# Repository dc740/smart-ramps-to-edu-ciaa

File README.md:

# Smart-RAMPS to EDU-CIAA (Work in progress)
Adapter to be able to use a Smart RAMPS (3.3v) as an EDU-CIAA Poncho

It's not finished yet!

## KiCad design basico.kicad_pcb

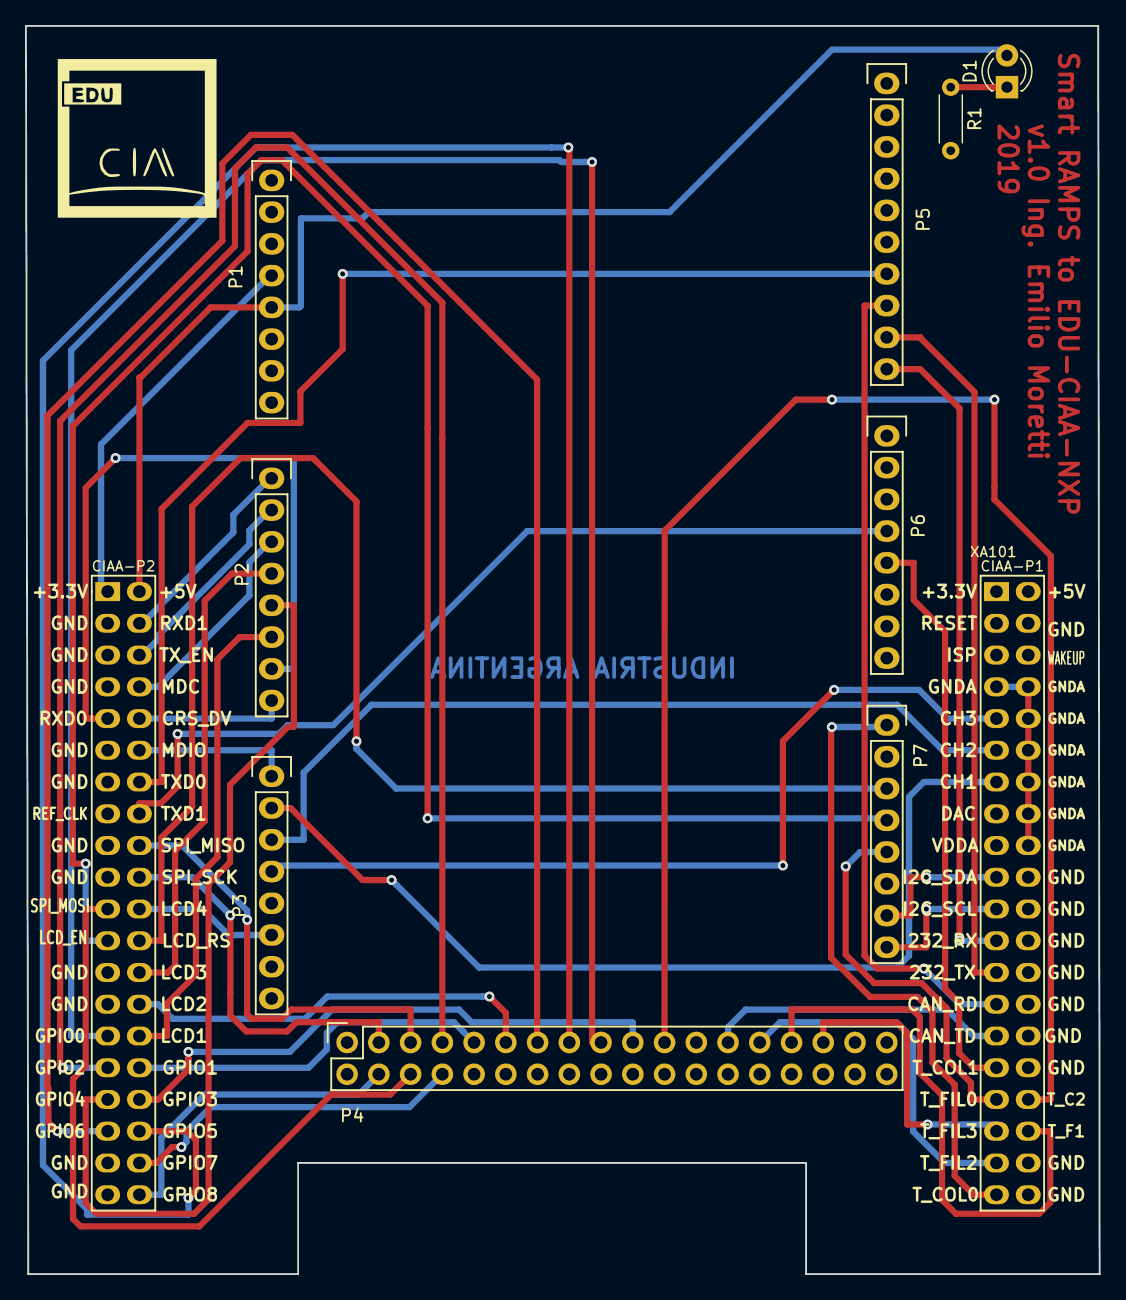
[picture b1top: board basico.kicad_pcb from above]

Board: 2 copper layers, 85.9 x 99.9 mm, 10 parts (0 on the bottom side), 46 nets.

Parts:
D1: LED; LED_D3.0mm
P1: Power; Socket_Strip_Arduino_1x08
P2, P3: Analog; Socket_Strip_Arduino_1x08
P4: Digital; Socket_Strip_Arduino_2x18
P5: PWM; Socket_Strip_Arduino_1x10
P6: PWM; Socket_Strip_Arduino_1x08
P7: Communication; Socket_Strip_Arduino_1x08
R1: 10k; R_Axial_DIN0204_L3.6mm_D1.6mm_P5.08mm_Horizontal
XA101: Conn_Poncho2P_2x_20x2; Conn_Poncho_SinBorde

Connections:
+3.3VP: P1.4, XA101.41
+5V: D1.2, P1.5, XA101.42
/Ar_3: P6.5, XA101.31
/Ar_4: P6.4, XA101.56
/Ar_8: P5.10, XA101.23
/Ar_9: P5.9, XA101.25
/Ar_10: P5.8, XA101.27
/Ar_11: P5.7, XA101.54
/Ar_14: P7.1, XA101.39
/Ar_16: P7.3, XA101.64
/Ar_17: P7.4, XA101.63
/Ar_18: P7.5, XA101.33
/Ar_20: P7.7, XA101.19
/Ar_21: P7.8, XA101.21
/Ar_24: P4.31, XA101.35
/Ar_26: P4.29, XA101.36
/Ar_28: P4.27, XA101.37
/Ar_30: P4.25, XA101.29
/Ar_34: P4.21, XA101.34
/Ar_36: P4.19, XA101.74
/Ar_38: P4.17, XA101.69
/Ar_40: P4.15, XA101.76
/Ar_42: P4.13, XA101.75
/Ar_44: P4.11, XA101.68
/Ar_46: P4.9, XA101.72
/Ar_48: P4.7, XA101.71
/Ar_49: P4.8, XA101.78
/Ar_50: P4.5, XA101.58
/Ar_51: P4.6, XA101.61
/Ar_52: P4.3, XA101.60
/Ar_53: P4.4, XA101.80
/Ar_A0: P2.1, XA101.44
/Ar_A1: P2.2, XA101.46
/Ar_A2: P2.3, XA101.48
/Ar_A3: P2.4, XA101.66
/Ar_A4: P2.5, XA101.73
/Ar_A5: P2.6, XA101.70
/Ar_A6: P2.7, XA101.49
/Ar_A7: P2.8, XA101.50
/Ar_A8: P3.1, XA101.52
/Ar_A9: P3.2, XA101.13
/Ar_A10: P3.3, XA101.11
/Ar_A11: P3.4, XA101.9
/Ar_A13: P3.6, XA101.62
GND: P1.6, P1.7, P5.4, R1.2, XA101.7, XA101.8, XA101.10, XA101.12, XA101.14, XA101.16, XA101.18, XA101.38, XA101.40
unnamed: D1.1, R1.1

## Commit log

2019-06-03 Empezamos a mapear cada pin
2019-06-05 Mas actualizaciones de esquematico
2019-06-05 completado el esquematico
2019-06-05 Update PCB
2019-06-05 Remove unused components. Update PCB
2019-06-06 Fix wrong mapping for analog channels
2019-06-12 All routes done
2019-06-12 Fix unconnected pin
2019-06-12 Cleanup
2019-06-15 Add missing files
2019-06-17 Clean up and add copper text
2019-06-17 Update version number
2019-06-24 Update arduino sizes
2019-06-25 Agregar led y re-ruteo
2019-06-26 Fix led
2019-06-26 Connect analog ground
2019-06-27 Add fixes and correct tracks

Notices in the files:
basico.kicad_pcb:
Licencia GPL v3 (Emilio Moretti - UNNOBA)
